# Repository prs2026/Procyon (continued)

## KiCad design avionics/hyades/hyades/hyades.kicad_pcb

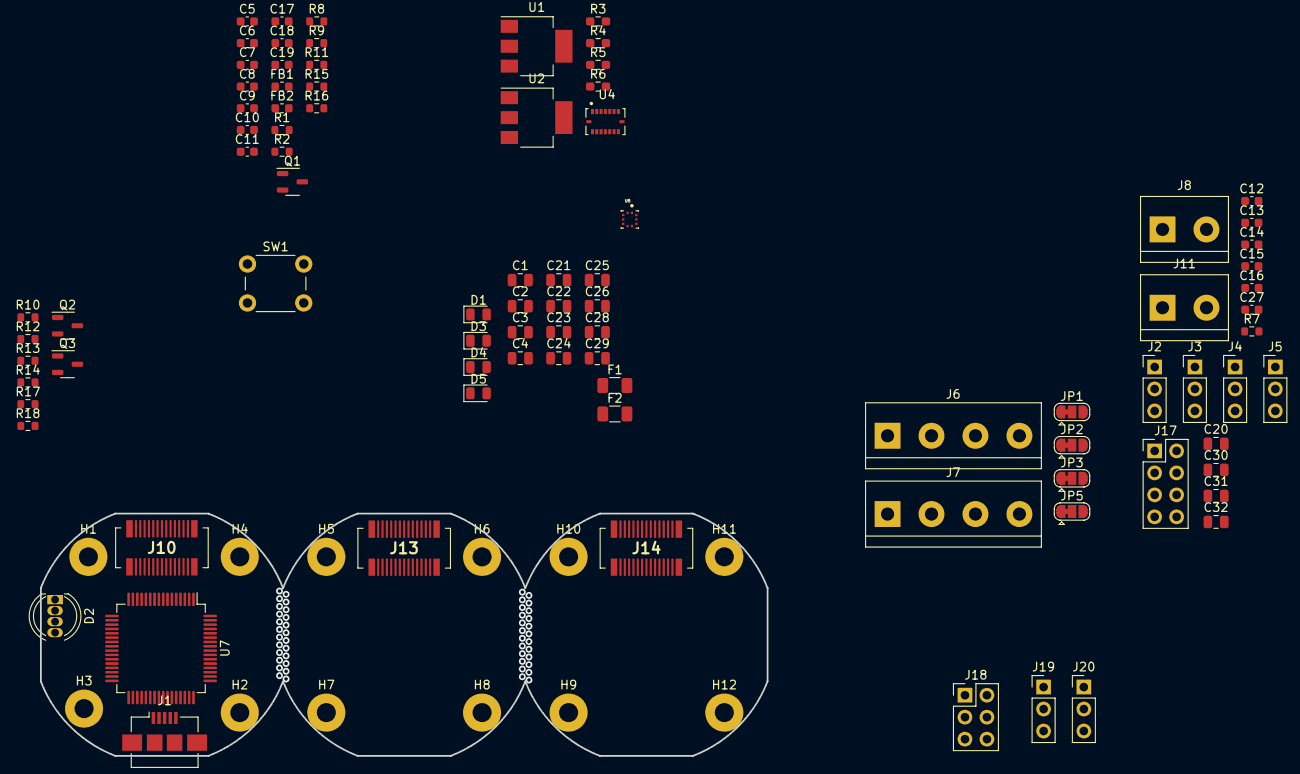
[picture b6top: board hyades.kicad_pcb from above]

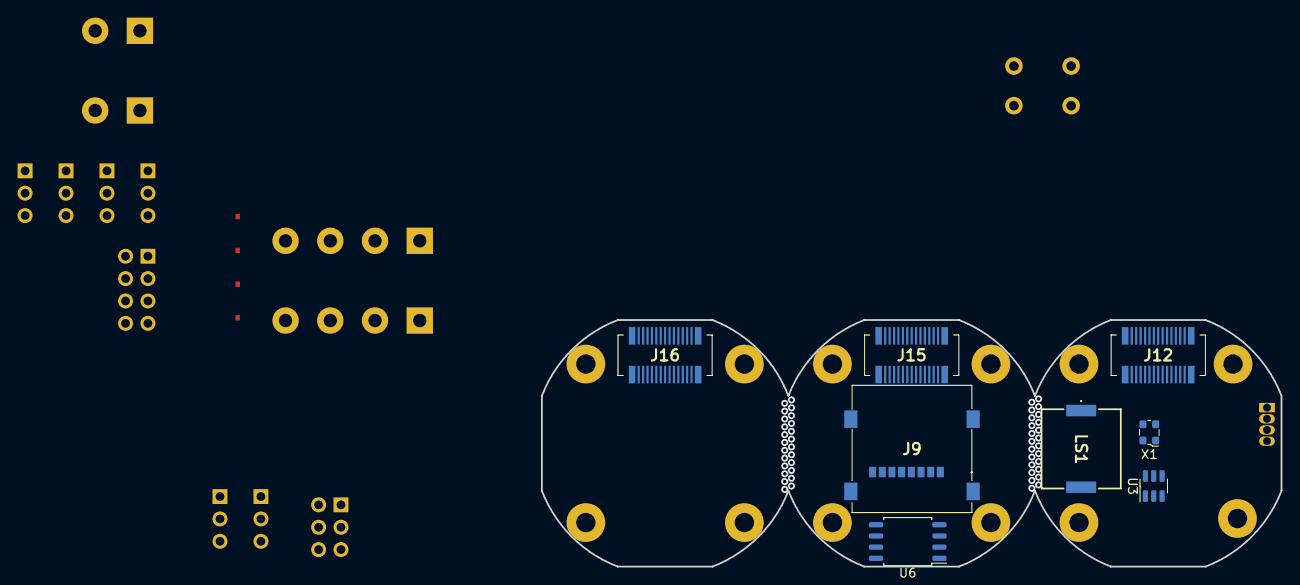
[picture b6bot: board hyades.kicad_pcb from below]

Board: 4 copper layers, 84.0 x 28.0 mm, 108 parts (8 on the bottom side), 63 nets, no tracks yet.

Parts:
C1, C2: 0.1uf; C_0805_2012Metric
C3, C4, C21, C22, C23, C24, C25, C26, C29: 1uf; C_0805_2012Metric
C5, C6, C7, C8, C10, C19: 0.1uf; C_0603_1608Metric
C9, C17, C18: 1uf; C_0603_1608Metric
C11, C12, C13, C14, C15, C16, C27: 100nf; C_0603_1608Metric
C20, C30, C31, C32: 100uf; C_0805_2012Metric
C28: 2u2; C_0805_2012Metric
D1: D_Small; D_0805_2012Metric
D2: LED_GKRB; LED_D5.0mm-4_RGB
D3, D4, D5: LED; LED_0805_2012Metric
F1: 2a; Fuse_1206_3216Metric
F2: 200ma; Fuse_1206_3216Metric
FB1: 600 @600mhz; L_0603_1608Metric
FB2: 600 @ 600MHz; L_0603_1608Metric
H1, H2, H3, H4, H5, H6, H7, H8, H9, H10, H11, H12: MountingHole_Pad; MountingHole_2.2mm_M2_Pad
J1: USB_B_Micro; USB_Micro-B_Amphenol_10104110_Horizontal
J2: Servo1; PinHeader_1x03_P2.54mm_Vertical
J3: Servo2; PinHeader_1x03_P2.54mm_Vertical
J4: Servo3; PinHeader_1x03_P2.54mm_Vertical
J5: Servo4; PinHeader_1x03_P2.54mm_Vertical
J6, J7: Screw_Terminal_01x04; TerminalBlock_bornier-4_P5.08mm
J8: Batt Terminal; TerminalBlock_bornier-2_P5.08mm
J9: MEM2067-02-180-00-A; MEM20670218000A
J10, J15, J16: BOARDTOBOARDB; AXK5S30347YG
J11: Switch Terminal; TerminalBlock_bornier-2_P5.08mm
J12, J13, J14: BOARDTOBOARDF; AXK5S30347YG
J17: Conn_02x04_Odd_Even; PinHeader_2x04_P2.54mm_Vertical
J18: SPI HEADER; PinHeader_2x03_P2.54mm_Vertical
J19: I2C HEADER; PinHeader_1x03_P2.54mm_Vertical
J20: UART HEADER; PinHeader_1x03_P2.54mm_Vertical
JP1: Servo Power; SolderJumper-3_P1.3mm_Bridged12_RoundedPad1.0x1.5mm
JP2: I2C POWER; SolderJumper-3_P1.3mm_Bridged12_RoundedPad1.0x1.5mm
JP3: UART POWER; SolderJumper-3_P1.3mm_Bridged12_RoundedPad1.0x1.5mm
JP5: SPI Power; SolderJumper-3_P1.3mm_Bridged12_RoundedPad1.0x1.5mm
LS1: PKMCS0909E4000-R1; PKMCS0909E4000R1
Q1: AO3401A; SOT-23-3
Q2, Q3: Q_NMOS_GSD; SOT-23-3
R1: 400; R_0603_1608Metric
R2: 1k5; R_0603_1608Metric
R3: 400; R_0603_1608Metric_Pad0.98x0.95mm_HandSolder
R4: 330; R_0603_1608Metric_Pad0.98x0.95mm_HandSolder
R5, R6: 240; R_0603_1608Metric_Pad0.98x0.95mm_HandSolder
R7, R8, R9, R11, R13, R17: 470; R_0603_1608Metric
R10: 20k; R_0603_1608Metric
R12: 6k; R_0603_1608Metric
R14, R18: 10; R_0603_1608Metric
R15, R16: 2k2; R_0603_1608Metric
SW1: SW_MEC_5E; SW_PUSH_6mm
U1, U2: LM317_SOT-223; SOT-223-3_TabPin2
U3: USBLC6-2SC6; SOT-23-6
U4: BMI088; PQFN50P450X300X100-16N
U5: BMP390L; XDCR_BMP390L
U6: W25Q32JVSS; SOIC-8_5.23x5.23mm_P1.27mm
U7: STM32F405RGTx; LQFP-64_10x10mm_P0.5mm
X1: ECS-2520MV-xxx-xx; Oscillator_SMD_ECS_2520MV-xxx-xx-4Pin_2.5x2.0mm

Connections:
+3.3VA: C18.2, C19.2, FB2.1, U7.13 (VDDA), X1.1 (Tri-State), X1.4 (VDD)
+3V3: C3.1, C5.1, C6.1, C7.1, C8.1, C9.2, C10.2, C12.2, C13.2, C14.2, C15.2, C16.2, C17.2, C21.1, C24.1, C26.1, C27.2, FB2.2, J6.2, J9.P4 (VDD), J10.1, J12.2, J13.2, J14.2, J15.1, J16.1, J17.8, JP2.3 (B), JP3.3 (B), JP5.3 (B), R2.1, R5.1, R8.2, R9.2, R11.2, R15.1, R16.1, U1.2 (VO), U4.3 (VDD), U4.7 (PS), U4.11 (VDDIO), U4.14 (CSB1), U5.1 (VDDIO), U5.6 (~CS), U5.10 (VDD), U6.3 (IO2), U6.7 (IO3), U6.8 (VCC), U7.1 (VBAT), U7.19 (VDD), U7.32 (VDD), U7.48 (VDD), U7.64 (VDD)
+5V: C4.1, C22.1, C23.1, C25.1, J10.4, J10.6, J12.3, J12.5, J13.3, J13.5, J14.3, J14.5, J15.4, J15.6, J16.4, J16.6, JP1.1 (A), JP2.1 (A), JP3.1 (A), JP5.1 (A), R6.1, U2.2 (VO)
+12P: F2.1, J6.3, J10.8, J10.10, J12.7, J12.9, J13.7, J13.9, J14.7, J14.9, J15.8, J15.10, J16.8, J16.10, J17.5, JP1.3 (B), Q1.2 (S)
+12V: C1.1, C2.1, D1.1 (K), FB1.2, R10.1, U1.3 (VI), U2.3 (VI)
+BATT: J8.1, J11.1
ACCEL INT1: J10.18, J12.17, J13.17, J14.17, J15.18, J16.18, U4.16 (INT1), U7.28 (PB2)
ACCEL INT2: J10.16, J12.15, J13.15, J14.15, J15.16, J16.16, U4.1 (INT2), U7.27 (PB1)
ARM+: J6.4, J7.1, J7.3
BARO INT: J10.24, J12.23, J13.23, J14.23, J15.24, J16.24, U5.7 (INT/DNC), U7.57 (PB5)
BATT SENSE: R10.2, R12.1, U7.15 (PA1)
BUZZER: LS1.1 (+), U7.58 (PB6)
CS SD: J9.P2 (CD/DAT3), J10.14, J12.13, J13.13, J14.13, J15.14, J16.14, U7.25 (PC5)
FLASH CS: J10.12, J12.11, J13.11, J14.11, J15.12, J16.12, U6.1 (~CS), U7.24 (PC4)
GND: C1.2, C2.2, C3.2, C4.2, C5.2, C6.2, C7.2, C8.2, C9.1, C10.1, C11.1, C12.1, C13.1, C14.1, C15.1, C16.1, C17.1, C18.1, C19.1, C20.1, C21.2, C22.2, C23.2, C24.2, C25.2, C26.2, C27.1, C28.2, C29.2, C30.1, C31.1, C32.1, D3.1 (K), D4.1 (K), D5.1 (K), H1.1, H2.1, H3.1, H4.1, H5.1, H6.1, H7.1, H8.1, H9.1, H10.1, H11.1, H12.1, J1.5 (GND), J2.3, J3.3, J4.3, J5.3, J6.1, J8.2, J9.P6 (VSS), J10.29, J10.30, J12.29, J12.30, J13.29, J13.30, J14.29, J14.30, J15.29, J15.30, J16.29, J16.30, J17.7, J18.3, LS1.2 (-), Q1.1 (G), Q2.2 (S), Q3.2 (S), R1.2, R4.2, R7.1, R12.2, R13.1, R17.1, SW1.1, U3.2 (GND), U4.4 (GNDA), U4.6 (GNDIO), U4.10 (SDO2), U4.15 (SDO1), U5.3 (VSS/GND), U5.5 (SDO/DNC/SA0), U5.8 (VSS/GND__1), U5.9 (VSS/GND__2), U6.4 (GND), U7.12 (VSSA), U7.18 (VSS), U7.63 (VSS), X1.2 (GND)
GYRO INT3: J10.20, J12.19, J13.19, J14.19, J15.20, J16.20, U4.12 (INT3), U7.55 (PB3)
GYRO INT4: J10.22, J12.21, J13.21, J14.21, J15.22, J16.22, U4.13 (INT4), U7.56 (PB4)
I2C POWER: C31.2, J19.1, JP2.2 (C)
LED BLUE: D2.4 (BA), U7.59 (PB7)
LED GREEN: D2.1 (GA), U7.61 (PB8)
LED RED: D2.3 (RA), U7.62 (PB9)
MISO: J9.P7 (DAT0), J10.23, J12.24, J13.24, J14.24, J15.23, J16.23, J18.5, U6.2 (DO(IO1)), U7.22 (PA6)
MOSI: J9.P3 (CMD), J10.25, J12.26, J13.26, J14.26, J15.25, J16.25, J18.6, U6.5 (DI(IO0)), U7.23 (PA7)
unnamed: D2.2 (K), R7.2
unnamed: D3.2 (A), R11.1
unnamed: D4.2 (A), R8.1
unnamed: D5.2 (A), R9.1
unnamed: F2.2, FB1.1
unnamed: F1.2, Q1.3 (D)
unnamed: Q2.3 (D), R14.2
unnamed: Q3.3 (D), R18.2
unnamed: R3.2, R4.1
unnamed: R1.1, R5.2, U1.1 (ADJ)
unnamed: R3.1, R6.2, U2.1 (ADJ)
unnamed: C29.1, U7.31 (VCAP_1)
unnamed: C28.1, U7.47 (VCAP_2)
OSCIN: U7.5 (PH0), X1.3 (OUT)
P1 EN: J10.26, J12.25, J13.25, J14.25, J15.26, J16.26, Q3.1 (G), R17.2, U7.33 (PB12)
P1-: J7.2, R18.1
P2 EN: J10.28, J12.27, J13.27, J14.27, J15.28, J16.28, Q2.1 (G), R13.2, U7.34 (PB13)
P2-: J7.4, R14.1
PB14: J10.27, J12.28, J13.28, J14.28, J15.27, J16.27, J17.1, U7.35 (PB14)
PB15: J10.7, J12.8, J13.8, J14.8, J15.7, J16.7, J17.2, U7.36 (PB15)
PC8: J10.2, J12.1, J13.1, J14.1, J15.2, J16.2, J18.2, U7.39 (PC8)
RESET: C11.2, SW1.2, U7.7 (NRST)
SCK: J9.P5 (CLK), J10.21, J12.22, J13.22, J14.22, J15.21, J16.21, J18.4, U6.6 (CLK), U7.21 (PA5)
SCL: J10.11, J12.12, J13.12, J14.12, J15.11, J16.11, J19.3, R15.2, U4.8 (SCL/SCK), U5.2 (SCK/SCL), U7.29 (PB10)
SDA: J10.9, J12.10, J13.10, J14.10, J15.9, J16.9, J19.2, R16.2, U4.9 (SDA/SDI), U5.4 (SDI/SDO/SDA), U7.30 (PB11)
SERVO1: J2.1, J10.13, J12.14, J13.14, J14.14, J15.13, J16.13, U7.37 (PC6)
SERVO2: J3.1, J10.15, J12.16, J13.16, J14.16, J15.15, J16.15, U7.38 (PC7)
SERVO3: J4.1, J10.17, J12.18, J13.18, J14.18, J15.17, J16.17, U7.40 (PC9)
SERVO4: J5.1, J10.19, J12.20, J13.20, J14.20, J15.19, J16.19, U7.26 (PB0)
SERVOPOWER: C20.2, J2.2, J3.2, J4.2, J5.2, JP1.2 (C)
SPI POWER: C30.2, J18.1, JP5.2 (C)
TOGGLED12V: F1.1, J11.2
UART POWER: C32.2, J20.1, JP3.2 (C)
USART2 RX: J10.5, J12.6, J13.6, J14.6, J15.5, J16.5, J20.3, U7.17 (PA3)
USART2 TX: J10.3, J12.4, J13.4, J14.4, J15.3, J16.3, J20.2, U7.16 (PA2)
USB CON D+: J1.3 (D+), R2.2, U3.3 (I/O2)
USB CON D-: J1.2 (D-), U3.1 (I/O1)
USB D+: U3.4 (I/O2), U7.45 (PA12)
USB D-: U3.6 (I/O1), U7.44 (PA11)
VBUS: D1.2 (A), J1.1 (VBUS), U3.5 (VBUS)

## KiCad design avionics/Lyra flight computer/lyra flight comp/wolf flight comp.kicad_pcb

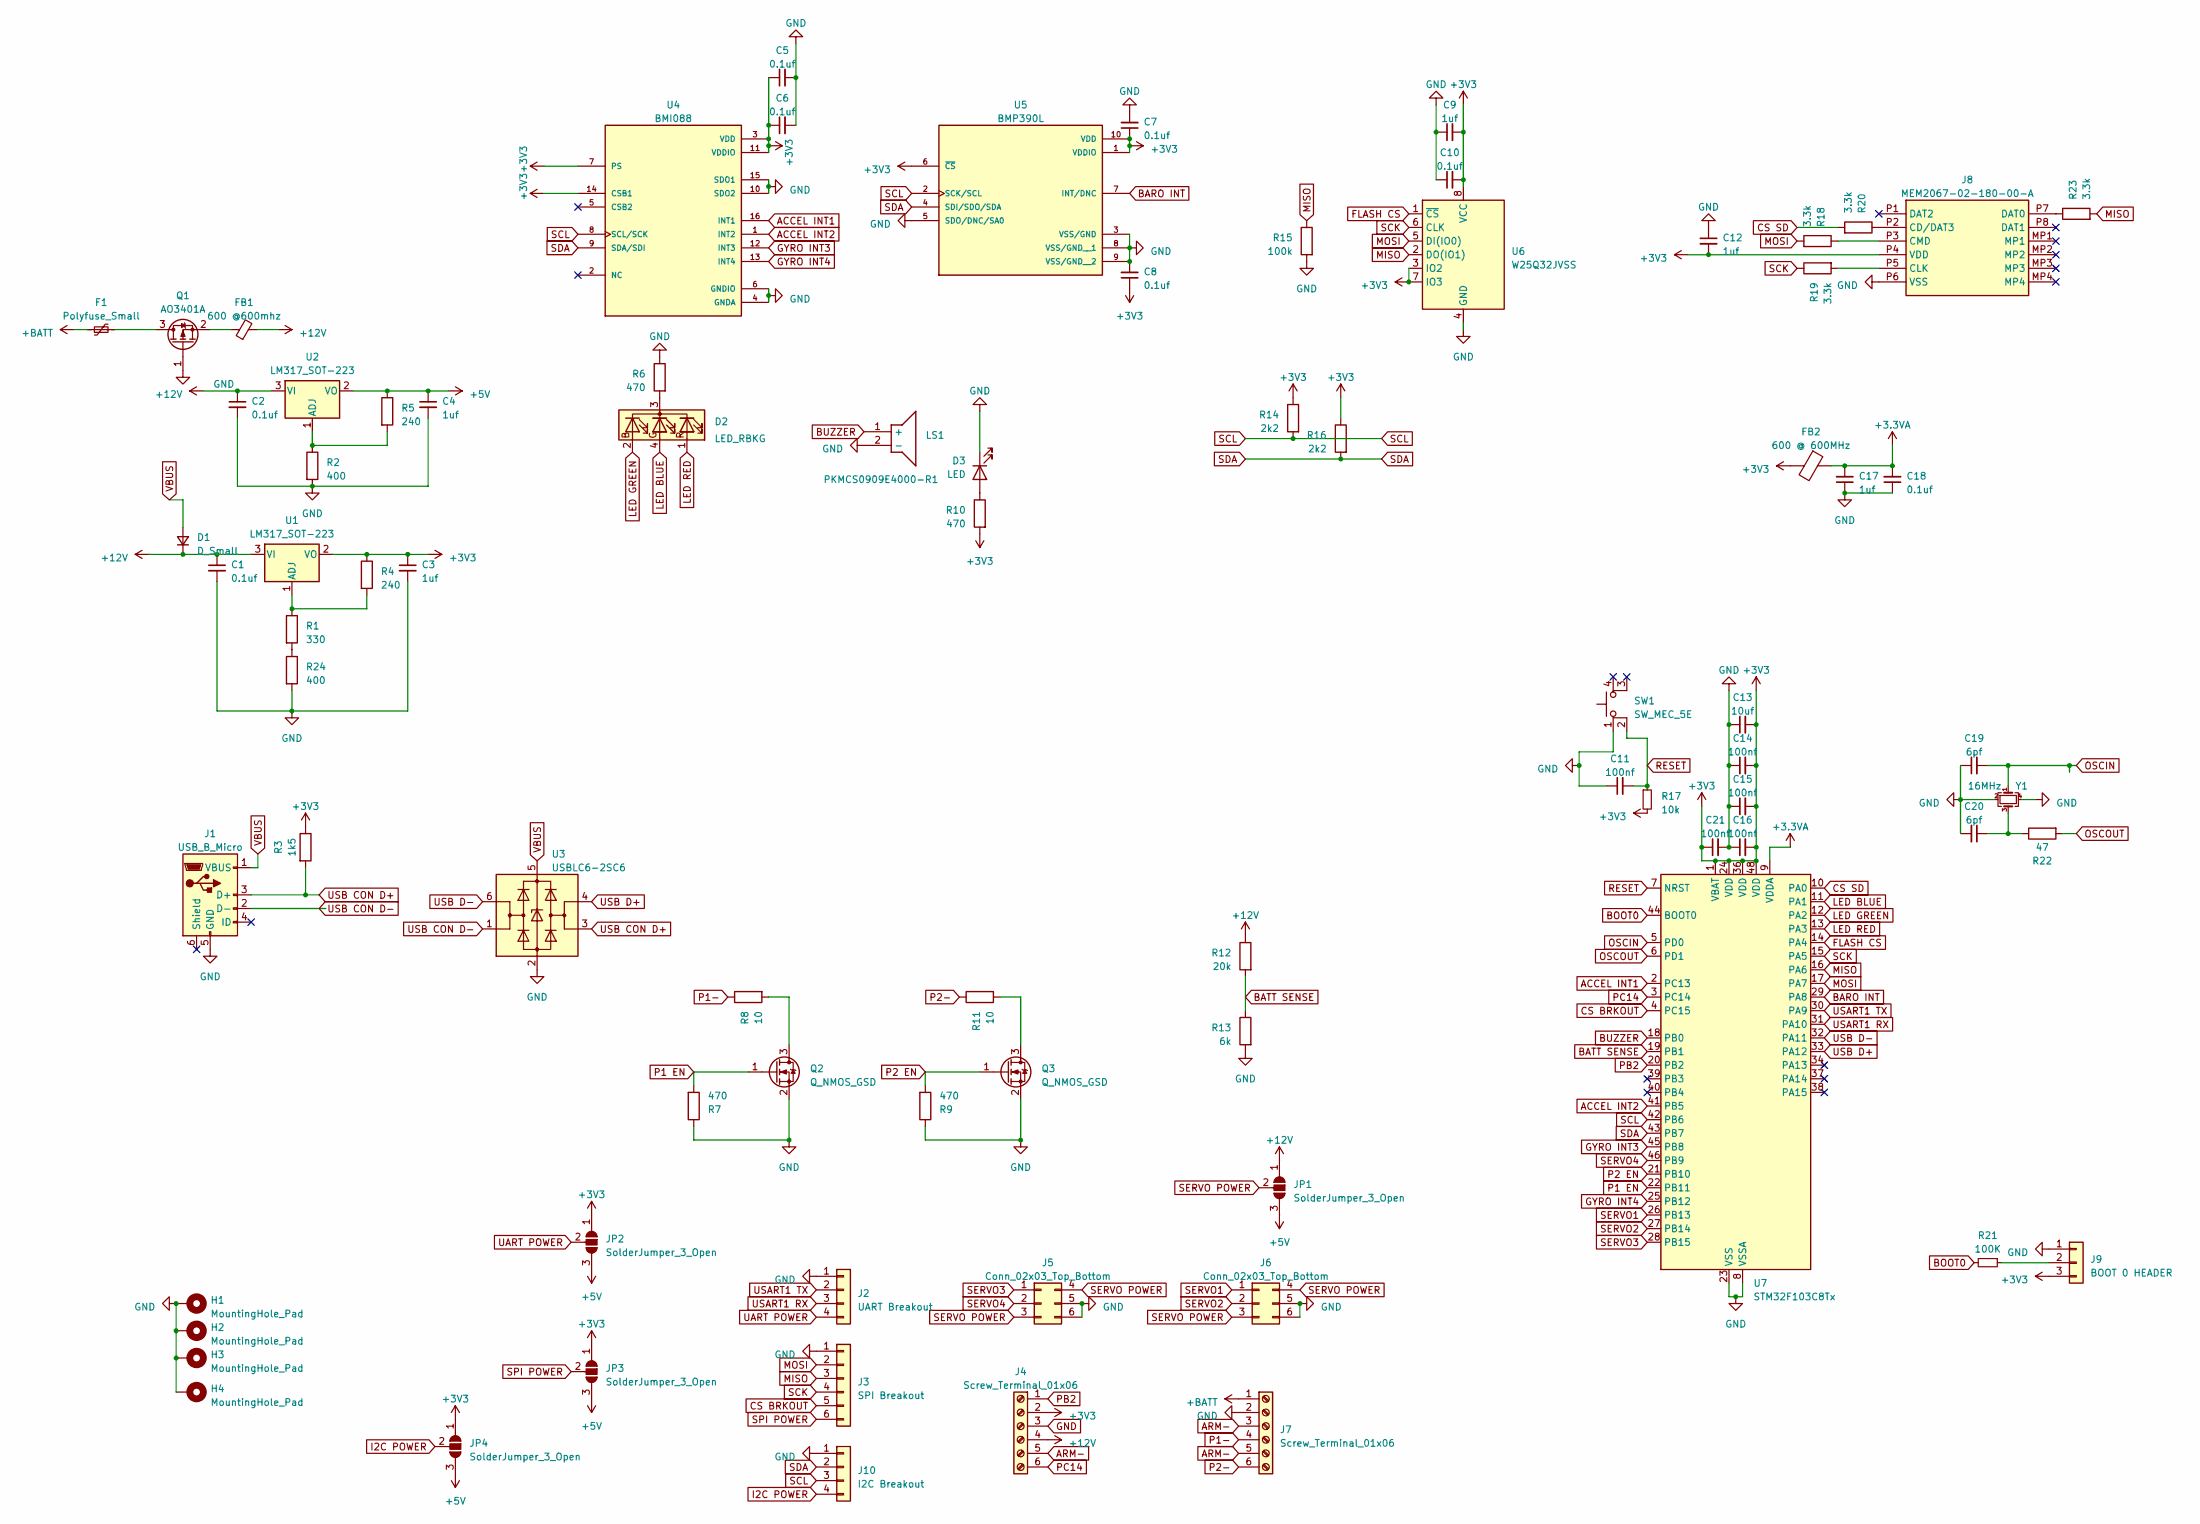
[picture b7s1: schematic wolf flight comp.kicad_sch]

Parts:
C1, C2: 0.1uf; C_0805_2012Metric
C3, C4: 1uf; C_0805_2012Metric
C5, C6, C7, C8, C10, C18: 0.1uf; C_0603_1608Metric
C9, C12, C17: 1uf; C_0603_1608Metric
C11, C14, C15, C16, C21: 100nf; C_0603_1608Metric
C13: 10uf; C_0805_2012Metric
C19, C20: 6pf; C_0603_1608Metric
D1: D_Small; D_0805_2012Metric
D2: LED_RBKG; LED_D5.0mm-4_RGB
D3: LED; LED_0805_2012Metric
F1: Polyfuse_Small; Fuse_1206_3216Metric
FB1: 600 @600mhz; L_0603_1608Metric
FB2: 600 @ 600MHz; L_0603_1608Metric
H1, H2, H3, H4: MountingHole_Pad; MountingHole_3.2mm_M3_DIN965_Pad
J1: USB_B_Micro; USB_Micro-B_Amphenol_10104110_Horizontal
J2: UART Breakout; PinHeader_1x04_P2.54mm_Vertical
J3: SPI Breakout; PinHeader_1x06_P2.54mm_Vertical
J4, J7: Screw_Terminal_01x06; TerminalBlock_Phoenix_MPT-0,5-6-2.54_1x06_P2.54mm_Horizontal
J5, J6: Conn_02x03_Top_Bottom; PinHeader_2x03_P2.54mm_Vertical
J8: MEM2067-02-180-00-A; MEM20670218000A; Mouser Part Number 640-MEM20670218000A
J9: BOOT 0 HEADER; PinHeader_1x03_P2.54mm_Vertical
J10: I2C Breakout; PinHeader_1x04_P2.54mm_Vertical
JP1, JP2, JP3, JP4: SolderJumper_3_Open; SolderJumper-3_P1.3mm_Open_Pad1.0x1.5mm
LS1: PKMCS0909E4000-R1; PKMCS0909E4000R1; Mouser Part Number 81-PKMCS0909E4000-R1
Q1: AO3401A; SOT-23-3
Q2, Q3: Q_NMOS_GSD; SOT-23-3
R1: 330; R_0603_1608Metric_Pad0.98x0.95mm_HandSolder
R2: 400; R_0603_1608Metric_Pad0.98x0.95mm_HandSolder
R3: 1k5; R_0603_1608Metric
R4, R5: 240; R_0603_1608Metric_Pad0.98x0.95mm_HandSolder
R6, R7, R9, R10: 470; R_0603_1608Metric
R8, R11: 10; R_0603_1608Metric
R12: 20k; R_0603_1608Metric
R13: 6k; R_0603_1608Metric
R14, R16: 2k2; R_0603_1608Metric
R15: 100k; R_0603_1608Metric
R17: 10k; R_0603_1608Metric
R18, R19, R20, R23: 3.3k; R_0603_1608Metric
R21: 100K; R_0603_1608Metric
R22: 47; R_0603_1608Metric
R24: 400; R_0603_1608Metric
SW1: SW_MEC_5E; SW_PUSH_6mm
U1, U2: LM317_SOT-223; SOT-223-3_TabPin2
U3: USBLC6-2SC6; SOT-666
U4: BMI088; PQFN50P450X300X100-16N
U5: BMP390L; XDCR_BMP390L; PARTREV 1.7
U6: W25Q32JVSS; SOIC-8_5.23x5.23mm_P1.27mm
U7: STM32F103C8Tx; LQFP-48_7x7mm_P0.5mm
Y1: 16MHz; Crystal_SMD_2520-4Pin_2.5x2.0mm; LCSC Part # C13738

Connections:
+3.3VA: C17.2, C18.2, FB2.1, U7.9 (VDDA)
+3V3: C3.1, C5.1, C6.1, C7.1, C8.1, C9.2, C10.2, C12.2, C13.2, C14.2, C15.2, C16.2, C21.1, FB2.2, J4.2, J8.P4 (VDD), J9.3, JP2.1 (A), JP3.1 (A), JP4.1 (A), R3.1, R4.1, R10.2, R14.1, R16.1, R17.2, U1.2 (VO), U4.3 (VDD), U4.7 (PS), U4.11 (VDDIO), U4.14 (CSB1), U5.1 (VDDIO), U5.6 (~CS), U5.10 (VDD), U6.3 (IO2), U6.7 (IO3), U6.8 (VCC), U7.1 (VBAT), U7.24 (VDD), U7.36 (VDD), U7.48 (VDD)
+5V: C4.1, JP1.3 (B), JP2.3 (B), JP3.3 (B), JP4.3 (B), R5.1, U2.2 (VO)
+12V: C1.1, C2.1, D1.1 (K), FB1.2, J4.4, JP1.1 (A), R12.1, U1.3 (VI), U2.3 (VI)
+BATT: F1.1, J7.1
ACCEL INT1: U4.16 (INT1), U7.2 (PC13)
ACCEL INT2: U4.1 (INT2), U7.41 (PB5)
ARM-: J4.5, J7.3, J7.5
BARO INT: U5.7 (INT/DNC), U7.29 (PA8)
BATT SENSE: R12.2, R13.1, U7.19 (PB1)
BOOT0: R21.2, U7.44 (BOOT0)
BUZZER: LS1.1 (+), U7.18 (PB0)
CS BRKOUT: J3.5, U7.4 (PC15)
CS SD: R20.2, U7.10 (PA0)
FLASH CS: U6.1 (~CS), U7.14 (PA4)
GND: C1.2, C2.2, C3.2, C4.2, C5.2, C6.2, C7.2, C8.2, C9.1, C10.1, C11.1, C12.1, C13.1, C14.1, C15.1, C16.1, C17.1, C18.1, C19.1, C20.2, C21.2, D3.1 (K), H1.1, H2.1, H3.1, H4.1, J1.5 (GND), J2.1, J3.1, J4.3, J5.5, J5.6, J6.5, J6.6, J7.2, J8.P6 (VSS), J9.1, J10.1, LS1.2 (-), Q1.1 (G), Q2.2 (S), Q3.2 (S), R2.2, R6.1, R7.1, R9.1, R13.2, R15.2, R24.2, SW1.1, U3.2 (GND), U4.4 (GNDA), U4.6 (GNDIO), U4.10 (SDO2), U4.15 (SDO1), U5.3 (VSS/GND), U5.5 (SDO/DNC/SA0), U5.8 (VSS/GND__1), U5.9 (VSS/GND__2), U6.4 (GND), U7.8 (VSSA), U7.23 (VSS), U7.35 (VSS), U7.47 (VSS), Y1.2, Y1.4
GYRO INT3: U4.12 (INT3), U7.45 (PB8)
GYRO INT4: U4.13 (INT4), U7.25 (PB12)
I2C POWER: J10.4, JP4.2 (C)
LED BLUE: D2.4 (GA), U7.11 (PA1)
LED GREEN: D2.2 (BA), U7.12 (PA2)
LED RED: D2.1 (RA), U7.13 (PA3)
MISO: J3.3, R15.1, R23.2, U6.2 (DO(IO1)), U7.16 (PA6)
MOSI: J3.2, R18.2, U6.5 (DI(IO0)), U7.17 (PA7)
unnamed: C20.1, R22.1, Y1.3
unnamed: D2.3 (K), R6.2
unnamed: D3.2 (A), R10.1
unnamed: J8.P2 (CD/DAT3), R20.1
unnamed: J8.P5 (CLK), R19.2
unnamed: J8.P3 (CMD), R18.1
unnamed: J8.P7 (DAT0), R23.1
unnamed: J9.2, R21.1
unnamed: F1.2, Q1.3 (D)
unnamed: FB1.1, Q1.2 (S)
unnamed: Q2.3 (D), R8.2
unnamed: Q3.3 (D), R11.2
unnamed: R1.2, R24.1
unnamed: R1.1, R4.2, U1.1 (ADJ)
unnamed: R2.1, R5.2, U2.1 (ADJ)
OSCIN: C19.2, U7.5 (PD0), Y1.1
OSCOUT: R22.2, U7.6 (PD1)
P1 EN: Q2.1 (G), R7.2, U7.22 (PB11)
P1-: J7.4, R8.1
P2 EN: Q3.1 (G), R9.2, U7.21 (PB10)
P2-: J7.6, R11.1
PB2: J4.1, U7.20 (PB2)
PC14: J4.6, U7.3 (PC14)
RESET: C11.2, R17.1, SW1.2, U7.7 (NRST)
SCK: J3.4, R19.1, U6.6 (CLK), U7.15 (PA5)
SCL: J10.3, R14.2, U4.8 (SCL/SCK), U5.2 (SCK/SCL), U7.42 (PB6)
SDA: J10.2, R16.2, U4.9 (SDA/SDI), U5.4 (SDI/SDO/SDA), U7.43 (PB7)
SERVO1: J6.1, U7.26 (PB13)
SERVO2: J6.2, U7.27 (PB14)
SERVO3: J5.1, U7.28 (PB15)
SERVO4: J5.2, U7.46 (PB9)
SERVO POWER: J5.3, J5.4, J6.3, J6.4, JP1.2 (C)
SPI POWER: J3.6, JP3.2 (C)
UART POWER: J2.4, JP2.2 (C)
USART1 RX: J2.3, U7.31 (PA10)
USART1 TX: J2.2, U7.30 (PA9)
USB CON D+: J1.3 (D+), R3.2, U3.3 (I/O2)
USB CON D-: J1.2 (D-), U3.1 (I/O1)
USB D+: U3.4 (I/O2), U7.33 (PA12)
USB D-: U3.6 (I/O1), U7.32 (PA11)
VBUS: D1.2 (A), J1.1 (VBUS), U3.5 (VBUS)

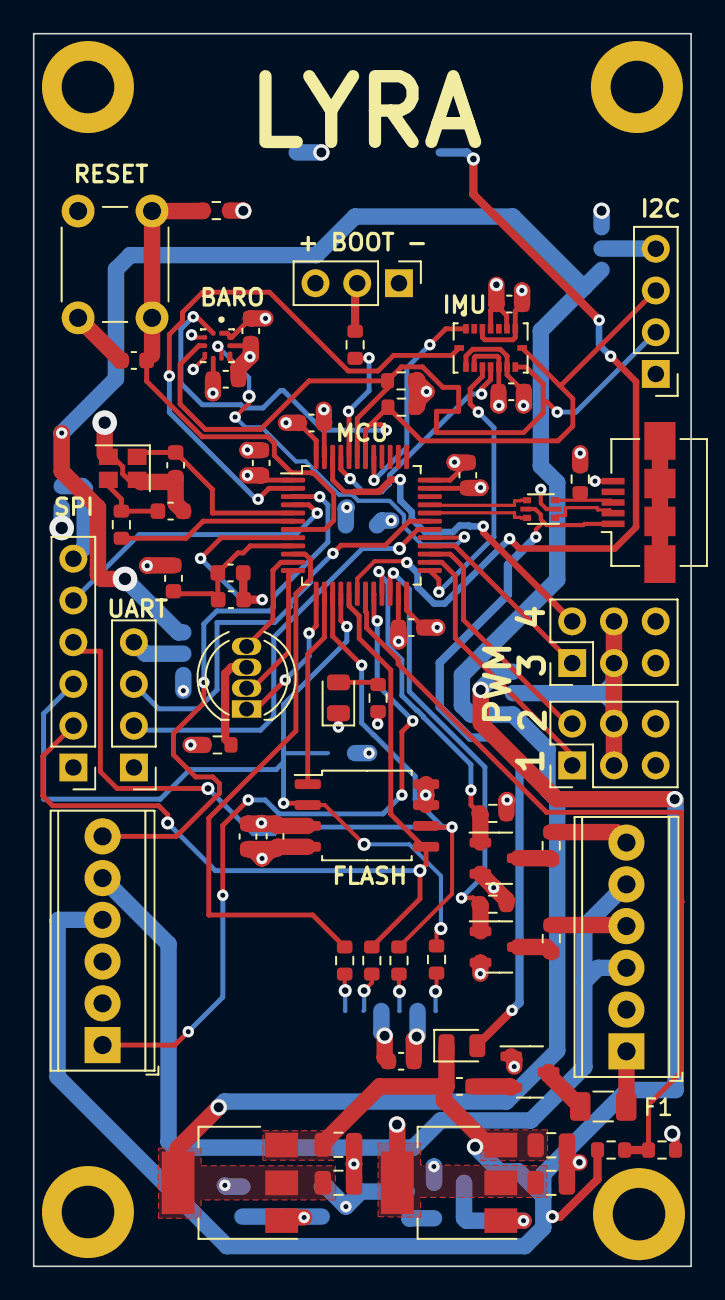
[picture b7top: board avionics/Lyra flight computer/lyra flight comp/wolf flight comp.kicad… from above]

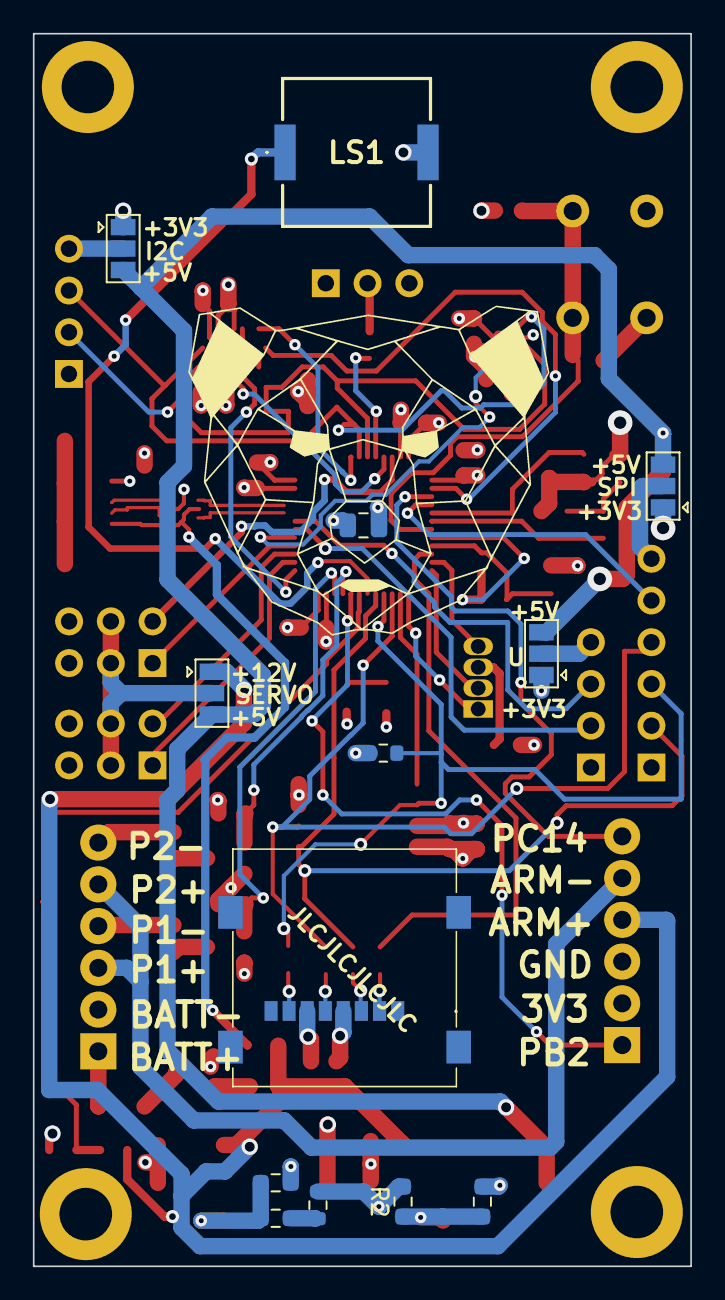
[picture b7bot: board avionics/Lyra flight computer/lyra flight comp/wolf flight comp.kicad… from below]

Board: 4 copper layers, 40.0 x 75.0 mm, 82 parts (13 on the bottom side), 65 nets.

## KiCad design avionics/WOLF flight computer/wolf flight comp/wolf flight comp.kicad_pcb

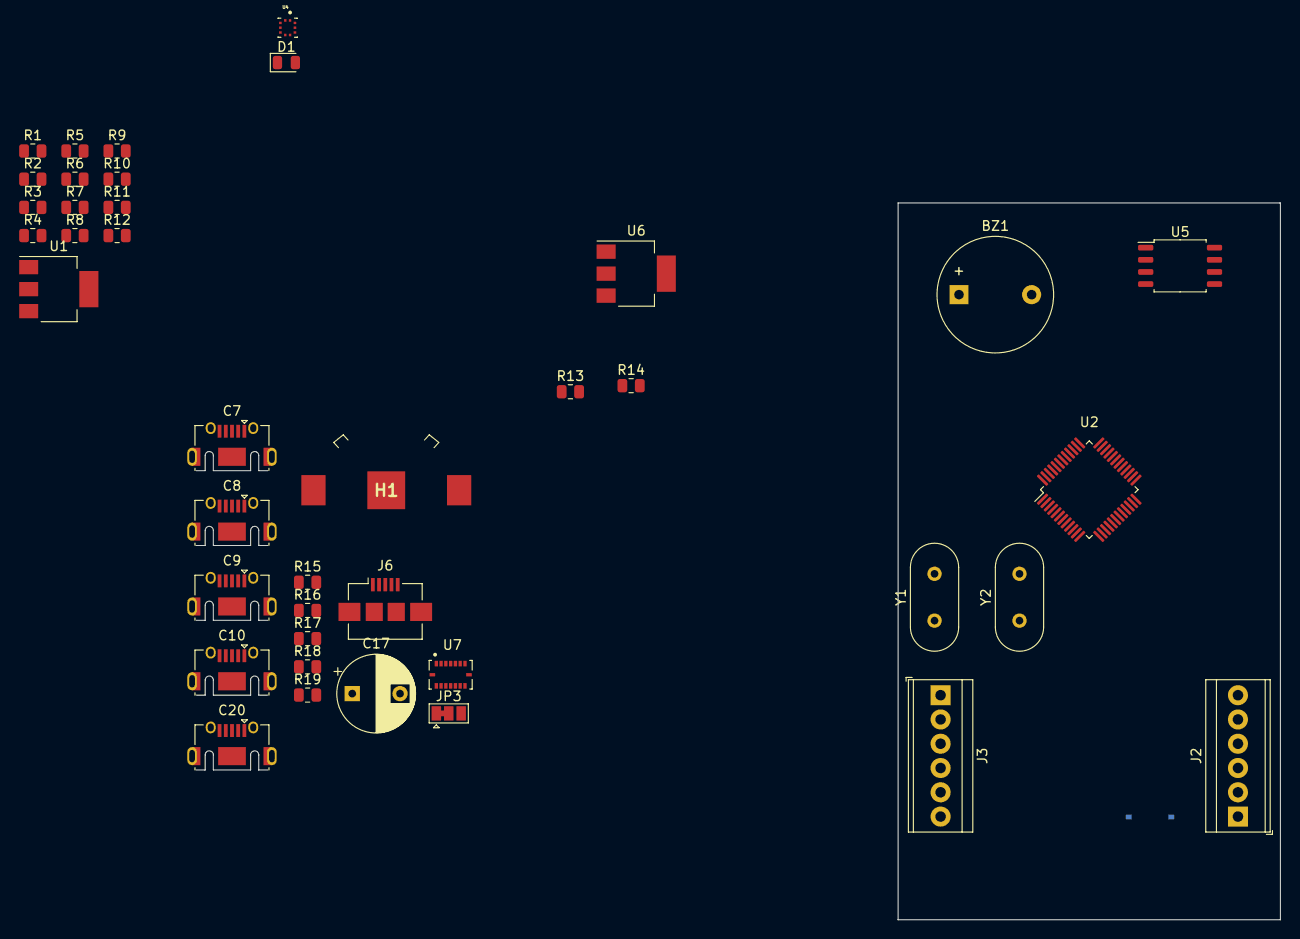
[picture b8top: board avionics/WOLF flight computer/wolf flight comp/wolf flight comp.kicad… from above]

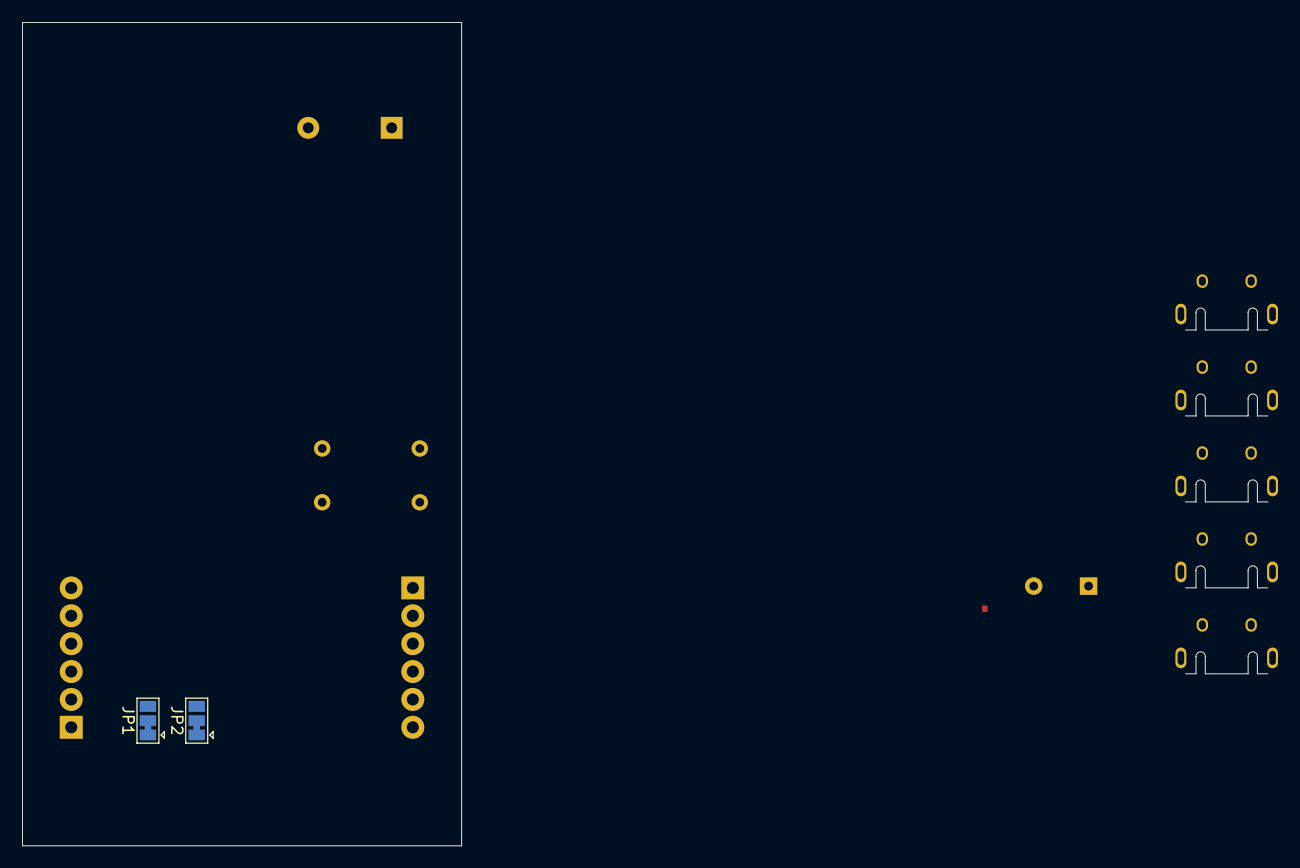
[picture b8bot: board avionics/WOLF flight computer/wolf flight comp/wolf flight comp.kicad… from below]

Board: 4 copper layers, 42 parts (2 on the bottom side), 36 nets, no tracks yet.

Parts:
BZ1: Buzzer; Buzzer_12x9.5RM7.6
C7: 10uf; USB_Micro-AB_Molex_47590-0001
C8, C9, C10, C20: 100nf; USB_Micro-AB_Molex_47590-0001
C17: 0.1uf; CP_Radial_D8.0mm_P5.00mm
D1: LED; LED_0805_2012Metric
H1: 2894
J2, J3: Screw_Terminal_01x06; TerminalBlock_TE_282834-6_1x06_P2.54mm_Horizontal
J6: USB_B_Micro; USB_Micro-B_Amphenol_10104110_Horizontal
JP1, JP2, JP3: SolderJumper_3_Bridged12; SolderJumper-3_P1.3mm_Bridged12_Pad1.0x1.5mm
R1: R; R_0805_2012Metric
R2: 240; R_0805_2012Metric
R3, R4: 20; R_0805_2012Metric
R5: 4.7K; R_0805_2012Metric
R6, R7: 470; R_0805_2012Metric
R8, R9, R18, R19: 0; R_0805_2012Metric
R10, R13, R14, R16, R17: 10k; R_0805_2012Metric
R11, R12: 100K; R_0805_2012Metric
R15: 100k; R_0805_2012Metric
U1: LM317_SOT-223; SOT-223-3_TabPin2
U2: STM32F103C8Tx; LQFP-48_7x7mm_P0.5mm
U4: BMP390L; XDCR_BMP390L
U5: W25Q32JVSS; SOIC-8_5.23x5.23mm_P1.27mm
U6: LM7805_TO220; SOT-223-3_TabPin2
U7: BMI088; PQFN50P450X300X100-16N
Y1: 32.768; Crystal_HC18-U_Vertical
Y2: 8MHZ; Crystal_HC18-U_Vertical

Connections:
+3V3: C7.2, C8.2, C9.2, C10.2, C20.2, JP1.3 (B), JP2.3 (B), R2.1, R6.2, R10.2, R13.1, R14.1, U1.2 (VO), U2.24 (VDD), U2.36 (VDD), U2.48 (VDD), U4.1 (VDDIO), U4.6 (~CS), U4.10 (VDD), U5.3 (IO2), U5.7 (IO3), U5.8 (VCC), U7.3 (VDD), U7.7 (PS), U7.11 (VDDIO), U7.14 (CSB1)
+BATT: J2.1, R16.1
BATT: C17.1, U1.3 (VI), U6.1 (VI)
BATT SENSE: R16.2, R17.1
BOOT0: R11.2, U2.44 (BOOT0)
BOOT1: R12.2, U2.20 (PB2)
BUZZER: BZ1.1 (-), U2.45 (PB8)
GND: BZ1.2 (+), C7.1, C8.1, C9.1, C10.1, C17.2, D1.1 (K), H1.MP1, J2.2, J3.3, J6.4 (ID), J6.5 (GND), J6.6 (Shield), JP1.1 (A), JP2.1 (A), R1.2, R7.1, R15.2, R17.2, U2.8 (VSSA), U2.23 (VSS), U2.35 (VSS), U2.47 (VSS), U4.3 (VSS/GND), U4.5 (SDO/DNC/SA0), U4.8 (VSS/GND__1), U4.9 (VSS/GND__2), U5.4 (GND), U6.2 (GND), U7.4 (GNDA), U7.6 (GNDIO), U7.10 (SDO2), U7.15 (SDO1)
MISO: R15.1, U2.16 (PA6), U5.2 (DO(IO1))
MOSI: U2.17 (PA7), U5.5 (DI(IO0))
unnamed: R8.1, Y1.2
unnamed: R9.1, Y1.1
unnamed: R19.1, Y2.2
unnamed: R18.1, Y2.1
unnamed: D1.2 (A), R6.1
unnamed: J6.1 (VBUS), R5.1
unnamed: H1.1 (+), H1.2 (-), JP3.1 (A)
unnamed: J6.3 (D+), R3.2
unnamed: J6.2 (D-), R4.1
unnamed: JP1.2 (C), R11.1
unnamed: JP2.2 (C), R12.1
unnamed: C20.1, JP3.3 (B)
unnamed: R1.1, R2.2, U1.1 (ADJ)
OSCIN: R19.2, U2.5 (PD0)
OSCIN2: R8.2, U2.3 (PC14)
OSCOUT: R18.2, U2.6 (PD1)
OSCOUT2: R9.2, U2.4 (PC15)
RESET: R10.1, U2.7 (NRST)
SCK: U2.15 (PA5), U5.6 (CLK)
SCL: J3.2, R13.2, U2.42 (PB6), U4.2 (SCK/SCL), U7.8 (SCL/SCK)
SDA: J3.1, R14.2, U2.43 (PB7), U4.4 (SDI/SDO/SDA), U7.9 (SDA/SDI)
USART1 RX: J3.4, U2.31 (PA10)
USART1 TX: J3.5, U2.30 (PA9)
USB D+: R3.1, R5.2, U2.33 (PA12)
USB D-: R4.2, U2.32 (PA11)
VBAT: JP3.2 (C), U2.1 (VBAT)

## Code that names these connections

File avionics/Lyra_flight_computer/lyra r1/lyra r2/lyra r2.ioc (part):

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Mcu.Name=STM32F415RGTx
Mcu.Package=LQFP64
Mcu.UserName=STM32F415RGTx
PA0-WKUP.Signal=S_TIM2_CH1_ETR
PA1.Signal=S_TIM2_CH2
PA11.Mode=Device_Only
PA11.Signal=USB_OTG_FS_DM
PA12.Mode=Device_Only
PA12.Signal=USB_OTG_FS_DP
PA13.Mode=Trace_Asynchronous_SW
PA13.Signal=SYS_JTMS-SWDIO
PA14.Mode=Trace_Asynchronous_SW
PA14.Signal=SYS_JTCK-SWCLK
PA2.Signal=S_TIM2_CH3
PA3.Signal=S_TIM5_CH4
PA4.Signal=GPIO_Output
PA5.Mode=Full_Duplex_Master
PA5.Signal=SPI1_SCK
PA6.Mode=Full_Duplex_Master
PA6.Signal=SPI1_MISO
PA7.Mode=Full_Duplex_Master
PA7.Signal=SPI1_MOSI
PB0.Signal=GPIO_Output
PB1.Signal=GPIO_Output
PB11.Signal=S_TIM2_CH4
PB3.Mode=Trace_Asynchronous_SW
PB3.Signal=SYS_JTDO-SWO
PB4.Signal=GPXTI4
PB5.Signal=GPXTI5
PB6.Mode=I2C
PB6.Signal=I2C1_SCL
PB7.Mode=I2C
PB7.Signal=I2C1_SDA
PB8.Signal=GPXTI8
PB9.Signal=GPXTI9
PC10.Mode=Asynchronous
PC10.Signal=USART3_TX
PC11.Mode=Asynchronous
PC11.Signal=USART3_RX
PC13-ANTI_TAMP.Signal=GPXTI13
PC14-OSC32_IN.Signal=GPXTI14
PC2.Signal=ADCx_IN12
PC3.Signal=ADCx_IN13
PC4.Signal=GPIO_Output
PC5.Signal=GPIO_Output
PC6.Signal=S_TIM3_CH1
PC7.Signal=S_TIM3_CH2
PC8.Signal=S_TIM3_CH3
PC9.Signal=S_TIM3_CH4
PH0-OSC_IN.Signal=RCC_OSC_IN
RCC.HSE_VALUE=16000000
RCC.SYSCLKFreq_VALUE=16000000
board=custom

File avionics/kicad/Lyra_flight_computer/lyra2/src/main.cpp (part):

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Adafruit_BMP3XX bmp;


#define REDLED PA3
#define GREENLED PA2
#define BLUELED PA1

#define BUZZERPIN PB0

#define SCANI2C

#define FLASHSTARTADDRESS 0x10FFF

#define FLASHCS PA4
#define SDCS PA0
#define RADIO_CE PC15

#define PYRO1 PB11
#define PYRO2 PB10

// define colors to numbers for ease of use
#define RED 0
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
SPIFlash flash(FLASHCS,0xEF16);

HardwareSerial Seria(PA10,PA9);

RF24 radio(RADIO_CE,PC14);

Sd2Card card;

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  pinMode(BLUELED,OUTPUT);
  pinMode(FLASHCS,OUTPUT);
  pinMode(SDCS,OUTPUT);
  pinMode(PB2,OUTPUT);
  pinMode(PYRO1,OUTPUT);
  digitalWrite(FLASHCS,HIGH);
  digitalWrite(SDCS,HIGH);
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  Seria.println("\n\nrestart");
  //setting pinmodes
  configpins();
  pinMode(PB2,INPUT_PULLDOWN);

  //setting led defualt color
  setled(RED);

  //BMI088 initilization code
  Wire.setSCL(PB6);
  Wire.setSDA(PB7);
  Wire.begin();

  initimu();
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    parsecommand(incomingbyte);
  }
  
  if (digitalRead(PB2) == HIGH)
  {
    tone(BUZZERPIN,1000,100);
  }
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
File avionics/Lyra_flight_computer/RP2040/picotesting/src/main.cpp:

#include <Arduino.h>
#include <quats.h>
#include "generallib.h"
#include <Wire.h>
#include <Lyrav2sensors.h>

Quaternion base(1,0,0,0);
Quaternion base2(0,1,0,0);
Quaternion basetonorm(0,1,1,0);


#define PICO_DEFAULT_I2C_SCL_PIN I2C1_SCL
#define PICO_DEFAULT_I2C_SDA_PIN I2C1_SCL



void printquat(Quaternion q1){
    char result[65];
    sprintf(result,"w = %d.%d,x = %d.%di, y = %d.%dj, z = %d.%dk",int(q1.w*1000)/1000,int(q1.w*1000)%1000,int(q1.x*1000)/1000,int(q1.x*1000)%1000,int(q1.y*1000)/1000,int(q1.y*1000)%1000,int(q1.z*1000)/1000,int(q1.z*1000)%1000);
    Serial.println(result);
}



void setup() {
  MP.setuppins();
  MP.beep();
  // put your setup code here, to run once:
  pinMode(LEDRED,OUTPUT);
  pinMode(LEDGREEN,OUTPUT);
  pinMode(LEDBLUE,OUTPUT);
  
  digitalWrite(LEDRED, LOW);
  digitalWrite(LEDGREEN, HIGH);
  digitalWrite(LEDBLUE, HIGH);
  Serial.begin(115200);
  while (!Serial)
  {
    delay(100);
  }

  Wire1.begin();
  
  Serial.println("\n\nrestart");

  scani2c(i2c);

}

void setup1(){

}

void loop() {
  
  digitalWrite(LEDRED,LOW);
  delay(1000);
  digitalWrite(LEDRED,HIGH);
  delay(1000);
  Serial.println("loop");
  
  
  // put your main code here, to run repeatedly:
}



void loop1(){

}

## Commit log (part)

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2023-10-01 complentary filter working
2023-10-01 flash and sd working
2023-10-01 radio init working
2023-10-02 flash and sd and radio working
2023-10-02 adding low pass filter for gyro and accel
2023-10-03 radio not actually working + antenna firmware init
2023-10-03 update and new velorum or file
2023-10-04 dont remember, tried to get radio to work(still doesnt)
2023-10-05 radios moving data, but no conversion back to state yet
2023-10-06 got ground software running
2023-10-07 python desktop venv init, telemetry working
2023-10-07 telemetry more working, working on datalogging
2023-10-07 got post flight- data movement working
2023-10-07 telemetry working
2023-10-08 preflght commit
2023-10-08 new ork files
2023-10-09 more or stuff
2023-10-09 added more ground software commands
    get pad offsets
    zero baro
2023-10-10 some more stuff
2023-10-10 buttons working
2023-10-20 stuff
2023-10-20 new switching alpha
2023-10-22 post 'flight' stuff
2023-10-24 init kalman filter for alt
2023-10-24 kf init
2023-10-25 more kf, got it somewhat working but with lots of lag
2023-10-25 more stuff
2023-10-26 bunch of things
2023-10-27 update or files
2023-10-29 road trip stuffs
    more work on kf, got it a little better by decreasing the update frequency. trying out new orientation estimation stuff, mostly from accel but not really working. init active boi ork file
2023-10-29 more work on ork and lots of cad
2023-10-30 ork stuff
2023-10-30 kicad autosaves
2023-11-01 ork tweaks
2023-11-01 some av tweaks
    max recorded alt reset, more logging work
2023-11-03 or and kicad
2023-11-05 new dayta
2023-11-06 stuffs
2023-11-07 av stuff
    fastie init, new way to get orientation, logging filtered vvel and world accel
2023-11-07 processing init, more orientation work
    orientation work
2023-11-11 trying more orientation stuff
2023-11-12 hehe
2023-11-15 stufsfsfsfs
2023-11-15 move stuff to other repo
2023-11-18 projectsunrise init
2023-11-21 ork changes
2023-11-27 update some things
2023-12-23 update ork
2023-12-24 update orks
2023-12-30 bega
2024-01-01 Update vega.ork
    add fiberglass weight
2024-01-07 38spciela
2024-01-09 add files
2024-01-11 vegas
2024-01-28 updata
2024-02-01 stufs
2024-02-01 simming way to high
2024-02-04 post flight commit
2024-02-05 asdf
2024-02-10 6-1 nc
2024-02-10 styfs
2024-02-20 post flight
2024-02-21 sim files
2024-02-21 pre leaving
2024-02-27 edits
2024-03-04 hjfg
2024-03-08 some real weights
2024-03-14 new motor for 38 and bunch of othe rupdatesd
2024-03-14 54updated with k455
2024-03-20 sdfg
2024-03-23 memes
2024-04-08 bunch o stuff
2024-04-15 fghj
2024-04-24 add fiiles
2024-05-04 lots of simming on TTT
2024-05-08 sim work
2024-05-23 fgyujftgyhuifgvyujgvhbjk
2024-05-24 gyui
2024-05-27 updooted sims for straight coupler
2024-05-31 more booh sim work
2024-06-10 rokets
2024-06-22 catia init
2024-06-23 work
2024-06-24 more work, made renders
2024-06-25 ttt and lyra work
2024-06-25 fixed LE radii
    ohboytm
2024-06-26 mvoed all :/
2024-06-26 updated or with lmmoi and real cg
2024-07-03 wolrk
2024-07-05 strat files
2024-07-08 init snap ring motor
2024-07-08 upadtes
    up
2024-07-09 more work, back on the conical train
2024-07-10 more work, redid fins and got pitching freq working?
2024-07-11 av bay work
2024-07-12 more av bay work, added the bulkhead
2024-07-13 av bay just needs sled
2024-07-15 moire av bay work
2024-07-22 post far commit
2024-07-23 move to ttt
2024-07-28 memes, this TTT sim is now davidmotor
2024-08-29 stuff, tower cad
2024-08-29 mrfarenheit
2024-09-25 mustang (:
2024-09-25 updoots
2024-10-01 m10keater, need i say more
2024-10-21 post far uploaf
2024-10-21 awgitg
2024-11-04 fies
2024-11-29 short38 motor
2024-11-29 stl files
2024-12-01 kill switch cad and snap ring 38 cad
2024-12-03 hangoverinit
2024-12-03 38 motor
2024-12-15 dash
2024-12-15 Dash CAD
2024-12-24 yeah
2024-12-31 sienor citizen & daq
2025-01-03 kill switch work and seinor citzenwork
2025-01-07 IGNITOR WORK
2025-01-08 launchcontroller code
2025-01-08 lots of openrocketwork
2025-01-08 launch control box code working
2025-01-09 firing chargers
2025-01-24 gunlaunch
2025-01-24 ssutffs
2025-01-25 gunalunch better
2025-02-04 cursed
2025-02-05 blackout
2025-02-06 dort
2025-02-06 workin
2025-02-11 motor work
2025-02-12 add drawings
2025-02-12 fc edits and drawing
2025-02-14 updoot
2025-02-19 fixed masses and added bent steel LE
2025-02-20 worked
2025-02-28 uopdopots
2025-03-03 blackout flew and start relapse
2025-03-04 made 54 l1k p prop fiocyl chiller
2025-03-04 blackout and relapse daydreaming
2025-03-09 update flight data
2025-03-09 shotandchasercadandsim
2025-03-10 little bit of work
2025-03-11 catia why
    isc work
2025-03-14 cad ):
2025-03-19 buncha cad
2025-03-20 boostka L1200
2025-03-20 lil cad edits
2025-03-28 rehab and copper balls
2025-03-31 lotsa work
2025-04-01 cursed antennas
2025-04-06 boosta av bay and some fiddling about with sustainer av bay
2025-04-06 messed with sustainer av bay a bit more
2025-04-08 sustainer av bay work, change to bulkhead raven
2025-04-14 import acdc nd do the other things
2025-04-15 molded fin can cat part make
2025-04-17 bruhsteprocket
2025-04-20 bruhdotstep
2025-04-25 bruh.step cad
2025-04-26 new hei
2025-04-27 random sim fun
2025-05-06 bruhdotstepwork
2025-05-06 new nose assembly time
2025-05-07 relapse work
2025-05-24 lotsa cad work
2025-05-27 go pro cad
2025-06-09 code and cad
2025-06-09 stashed
2025-06-12 coyote pnid
2025-06-14 new sims with chase motors and more av bay work
2025-06-21 ply cads
2025-06-25 last commit with the old nose section with the go pro
2025-06-29 things
2025-07-18 preflight
2025-07-25 huhiforgortopush
2025-08-23 work work work
2025-08-26 phase change sink
2025-08-29 ras sim is borked
2025-09-01 overdose cad
2025-10-11 aluminum can
2025-10-11 wokr
2025-10-15 went with the printed fin can
2025-10-16 l3 and gps export
2025-10-17 rail (:
2025-12-03 asi, overdose, momentary lapse in reason, cert rockets
2026-01-15 rocketpy and updated relapse stuff
2026-01-15 lotsa cad changes and others
2026-01-15 other sim
2026-01-15 new overdose and relapse sims
2026-01-16 monte carlo stuff
2026-01-16 juliensim and similar, also shock cord winder and rigging jig
2026-01-16 monte carlo save and loading
2026-01-16 more work on monte carlo
2026-01-17 more monte carlo!!!!!
2026-01-20 work on drive to far
2026-01-21 other montecarlo work, imported openmeteodata
2026-01-21 more work and monte carlo on the booster
2026-01-22 places
2026-01-24 post far
2026-01-24 post recovery data whoring
2026-01-26 cad work
2026-01-26 l2 cert work
2026-01-27 single stage drawings
2026-01-29 jump cad
2026-02-18 work, l2 and reorganizing
2026-02-20 l2 cad work
2026-03-04 cvaf
2026-04-14 jump work and abj sims
2026-04-15 work on jump
2026-04-19 jump cad work
2026-04-21 ras update
2026-04-25 jump rocketpy sims
2026-04-28 messed with closure
2026-04-28 hecka jump cad and rocketpy work
2026-04-29 cad work (why am i here)
2026-05-07 lots of cad work, starting to print test pieces
2026-05-15 av bay and nozzle changes
2026-05-15 saving and junk
2026-05-21 hecka rocketpy stuff
2026-05-22 sustainer wiring schematic made and cad updated hecka for av bay
2026-05-24 phone holder, payload cad, etc
2026-05-30 av bay cad, sim updates, jig updates.
2026-06-06 rockeptyand caad
2026-06-06 relapse anyalsis update
2026-06-10 man what the fuck
2026-06-26 many things and cad cleanups
2026-06-26 whatever didnt make it last time
2026-06-29 huh the old thing didnt work
